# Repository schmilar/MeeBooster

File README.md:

# MeeBooster
Collection of 3 BoosterPacks for the Texas Instruments MSP432 Launchpad that aim to recreate the MeeBlip synthesizer on a different hardware platform.

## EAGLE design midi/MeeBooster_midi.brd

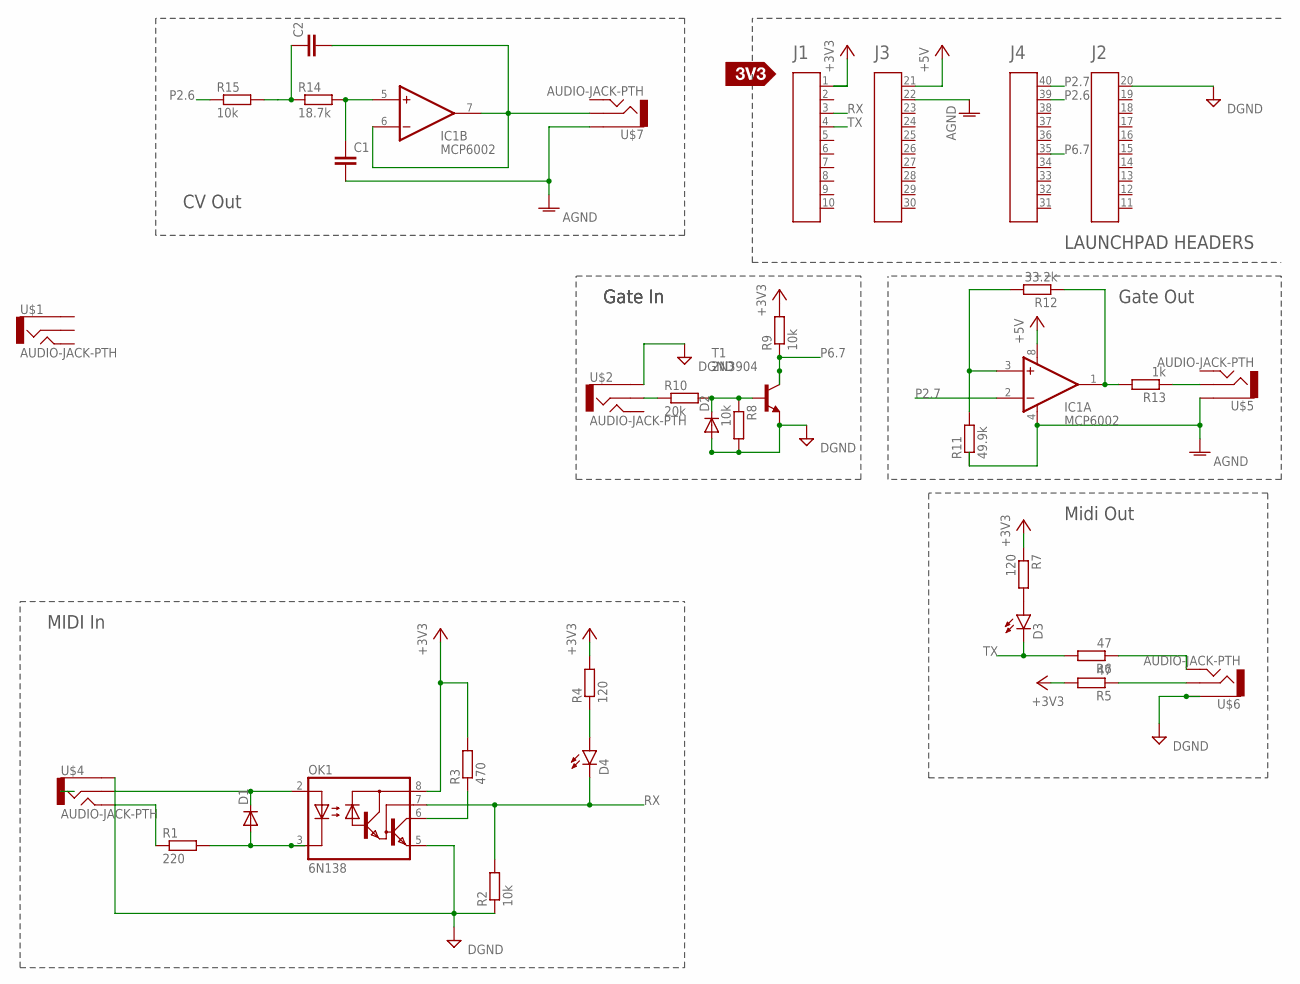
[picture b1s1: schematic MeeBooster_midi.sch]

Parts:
A1: HEADER4X10-BOOSTERPACK; 4X10-BOOSTERPACK
C1, C2: CAP0603-CAP; 0603-CAP
D1, D2: DIODE1N4148; DIODE-1N4148
D3, D4: LED5MM
IC1: MCP6002; DIL08
OK1: 6N138; DIL08
R1: 220; M1206
R2, R8, R9, R15: 10k; M1206
R3: 470; M1206
R4, R7: 120; M1206
R5, R6: 47; M1206
R10: 20k; M1206
R11: 49.9k; M1206
R12: 33.2k; M1206
R13: 1k; M1206
R14: 18.7k; M1206
T1: 2N3904; TO92
U$1, U$2, U$4, U$5, U$6, U$7: AUDIO-JACK-PTH; AUDIO-JACK
U$3: SILK_3V3_TAG

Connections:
5V: A1.1
+3V3: OK1.8 (VCC), R3.2, R4.2, R5.2, R7.1, R9.2
+5V: A1.21, IC1.8 (V+)
AGND: A1.22, C1.2, IC1.4 (V-), R11.1, U$5.1, U$7.1
DGND: A1.20, D2.A, OK1.5 (GND), R2.1, R8.2, T1.3 (E), U$2.1, U$4.1, U$6.1
unnamed: D1.C, OK1.2 (A), U$4.2
unnamed: D1.A, OK1.3 (C), R1.2
unnamed: D2.C, R8.1, R10.2, T1.2 (B)
unnamed: OK1.6 (VO), R3.1
unnamed: R1.1, U$4.5
unnamed: R5.1, U$6.2
unnamed: R6.1, U$6.5
unnamed: D3.A, R7.2
unnamed: D4.A, R4.1
unnamed: R10.1, U$2.2
unnamed: IC1.1 (OUT), R12.1, R13.2
unnamed: IC1.3 (+IN), R11.2, R12.2
unnamed: C2.2, IC1.6 (-IN), IC1.7 (OUT)
unnamed: R13.1, U$5.2
unnamed: C1.1, IC1.5 (+IN), R14.2
unnamed: C2.1, R14.1, R15.2
P2.6: A1.39, R15.1
P2.7: A1.40, IC1.2 (-IN)
P6.7: A1.35, R9.1, T1.1 (C)
RX: A1.3, D4.K (C), OK1.7 (VB), R2.2
TX: A1.4, D3.K (C), R6.2

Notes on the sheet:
LAUNCHPAD HEADERS
Midi Out
MIDI In
Gate In
Gate Out
CV Out

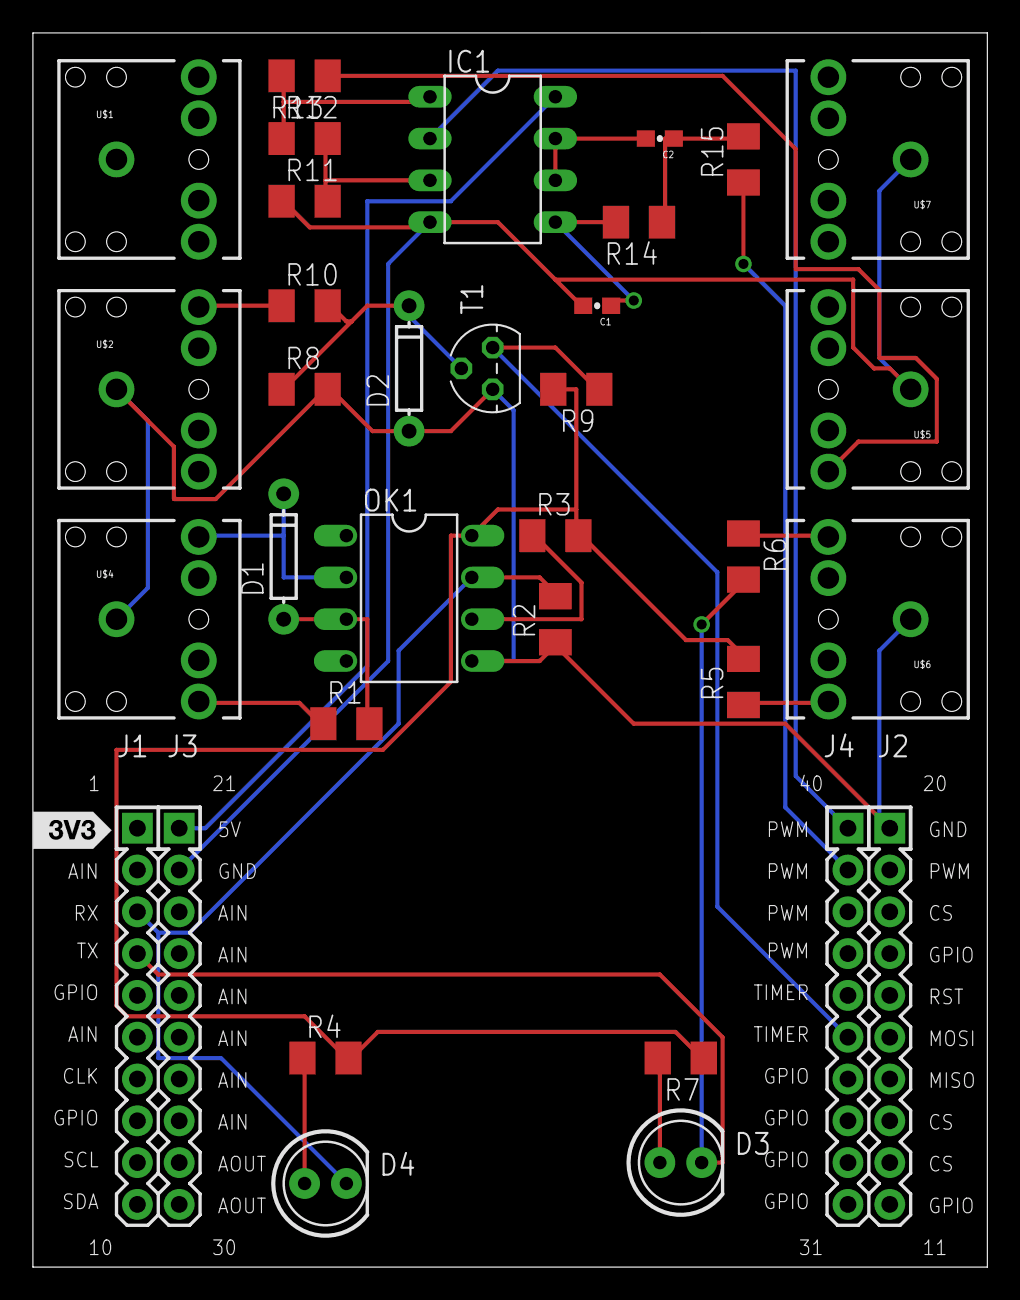
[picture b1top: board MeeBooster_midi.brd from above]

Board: 2 copper layers, 58.0 x 75.0 mm, 32 parts (0 on the bottom side), 25 nets.

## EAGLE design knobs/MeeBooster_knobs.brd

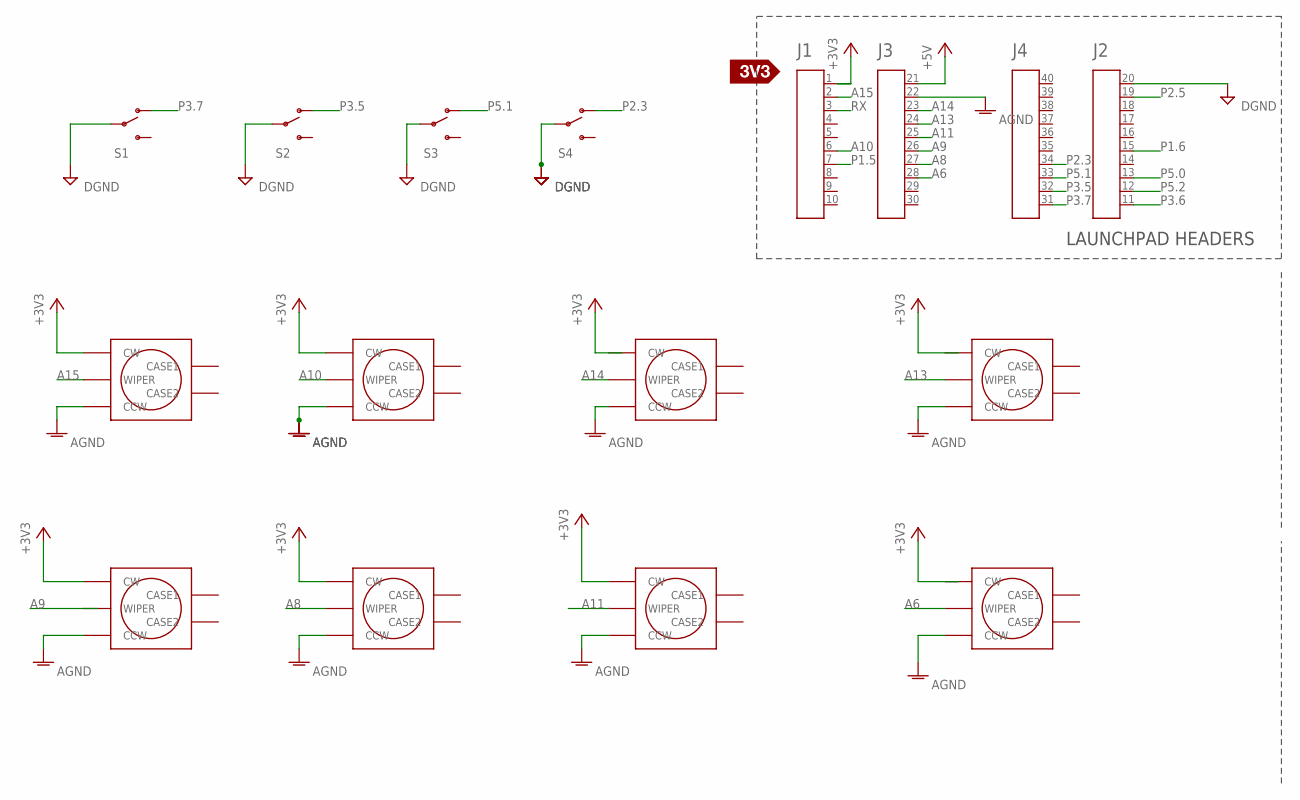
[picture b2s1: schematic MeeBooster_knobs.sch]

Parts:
A1: HEADER4X10-BOOSTERPACK; 4X10-BOOSTERPACK
S1, S2, S3, S4: SWITCH-SPSTPTH; SWITCH-SPDT
U$1, U$2, U$4, U$5, U$6, U$7, U$8, U$9: VACOLOCO_EVUFRK09_POT; VACOLOCO_EVUF
U$3: SILK_3V3_TAG

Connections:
5V: A1.1
+3V3: U$1.CW, U$2.CW, U$6.CW, U$7.CW, U$8.CW
+5V: A1.21
A6: A1.28, U$9.WIPER
A8: A1.27, U$7.WIPER
A9: A1.26
A10: A1.6, U$2.WIPER
A11: A1.25, U$8.WIPER
A13: A1.24, U$5.WIPER
A14: A1.23, U$4.WIPER
A15: A1.2, U$1.WIPER
AGND: A1.22, U$1.CCW, U$2.CCW, U$4.CCW, U$5.CCW, U$6.CCW, U$7.CCW, U$8.CCW, U$9.CCW
DGND: A1.20, S1.2, S2.2, S3.2, S4.2
P1.5: A1.7
P1.6: A1.15
P2.3: A1.34, S4.1 (O)
P2.5: A1.19
P3.5: A1.32, S2.1 (O)
P3.6: A1.11
P3.7: A1.31, S1.1 (O)
P5.0: A1.13
P5.1: A1.33, S3.1 (O)
P5.2: A1.12
RX: A1.3

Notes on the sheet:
LAUNCHPAD HEADERS

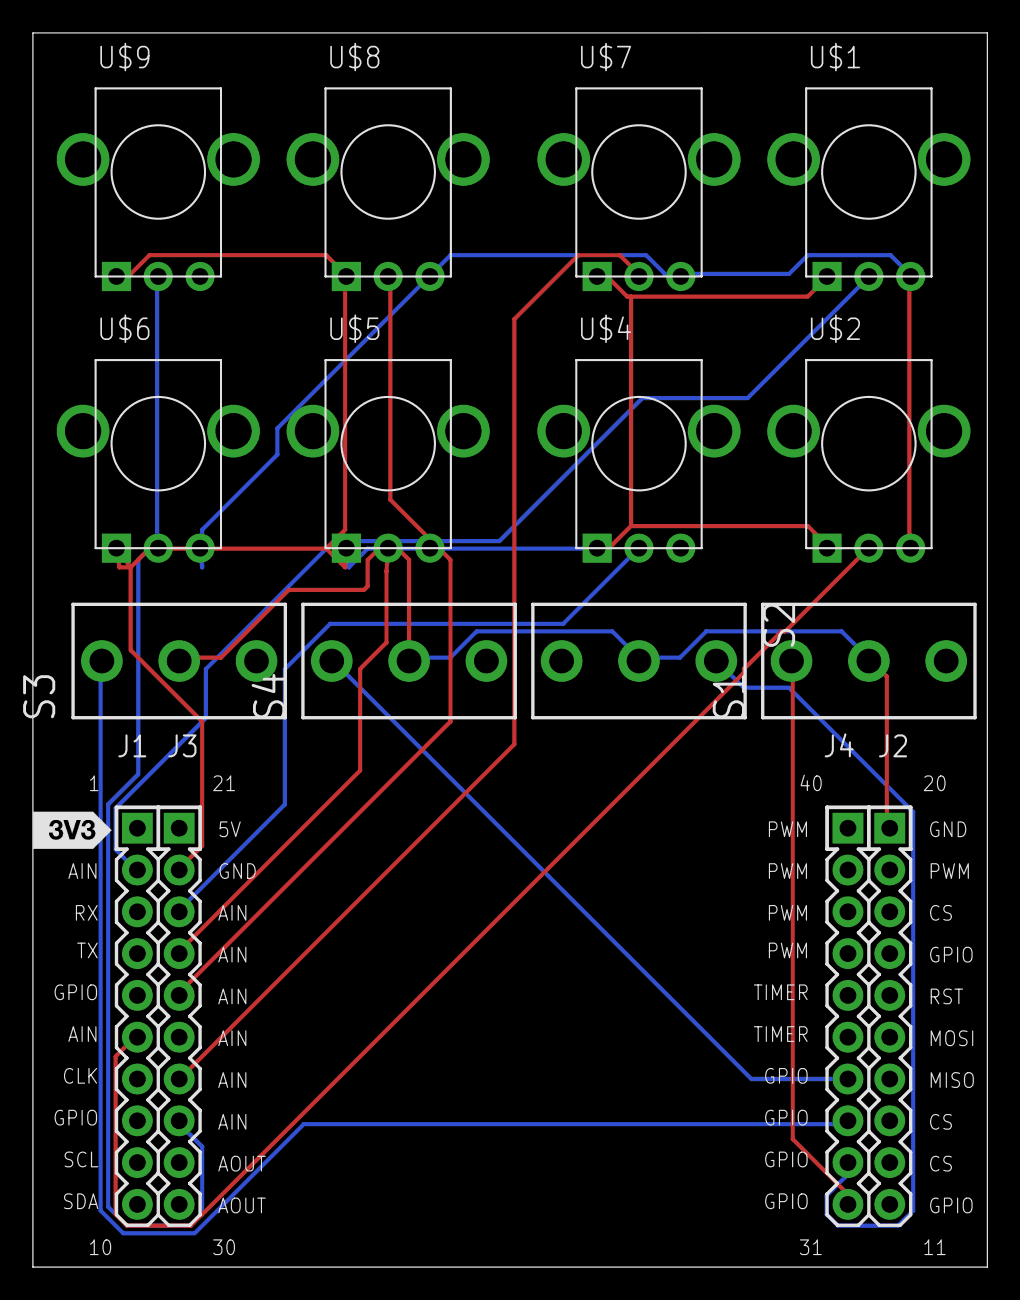
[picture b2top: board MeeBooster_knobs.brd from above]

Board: 2 copper layers, 58.0 x 75.0 mm, 14 parts (0 on the bottom side), 14 nets.

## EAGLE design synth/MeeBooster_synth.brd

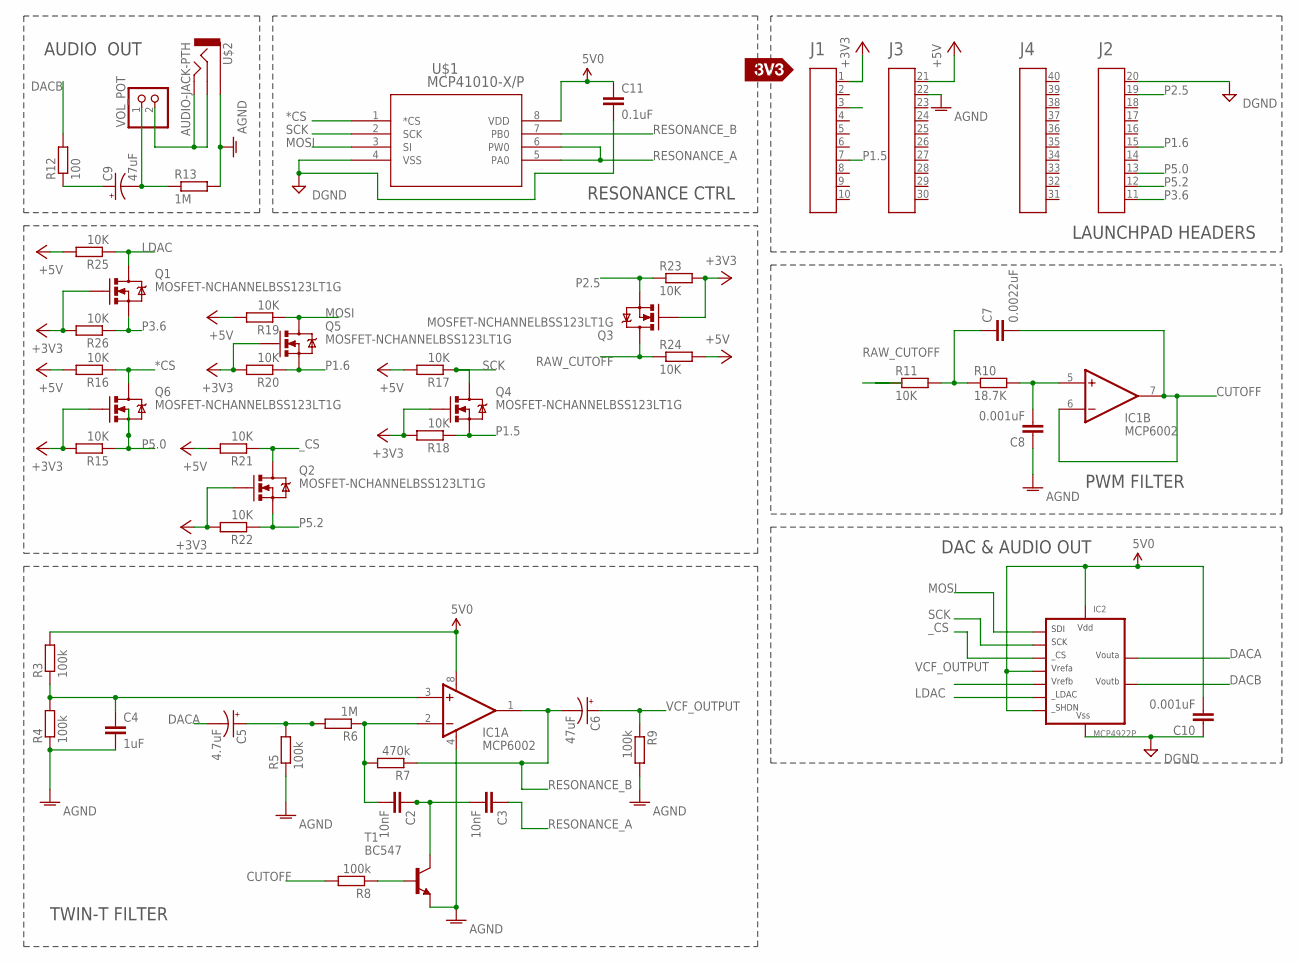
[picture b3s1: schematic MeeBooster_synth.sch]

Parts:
A1: HEADER4X10-BOOSTERPACK; 4X10-BOOSTERPACK
C2, C3: 10nF; 0603-CAP
C4: 1uF; 0603-CAP
C5: 4.7uF; PANASONIC_C
C6, C9: 47uF; PANASONIC_D
C7: 0.0022uF; 0603-CAP
C8, C10: 0.001uF; 0603-CAP
C11: 0.1uF; C0603
IC1: MCP6002; DIL08
IC2: MCP4922P; DIL14
Q1, Q2, Q3, Q4, Q5, Q6: MOSFET-NCHANNELBSS123LT1G; SOT23-3
R3, R4, R5, R8, R9: 100k; M1206
R6, R13: 1M; M1206
R7: 470k; M1206
R10: 18.7K; M1206
R11, R15, R16, R17, R18, R19, R20, R21, R22, R23, R24, R25, R26: 10K; M1206
R12: 100; M1206
T1: BC547; TO92
U$1: MCP41010-X/P; PDIP8_300MC
U$2: AUDIO-JACK-PTH; AUDIO-JACK
U$3: SILK_3V3_TAG
VOL_POT: PINHD-1X2; 1X02

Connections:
5V: A1.1, C10.2, C11.1, IC1.8 (V+), IC2.1 (VDD), IC2.9 (SHDN), IC2.13 (VREFA), R3.2, U$1.8 (VDD)
*CS: Q6.3 (D), R16.1, U$1.1 (*CS)
+3V3: Q1.1 (G), Q2.1 (G), Q3.1 (G), Q4.1 (G), Q5.1 (G), Q6.1 (G), R15.2, R18.2, R20.2, R22.2, R23.2, R26.2
+5V: A1.21, R16.2, R17.2, R19.2, R21.2, R24.2, R25.2
AGND: A1.22, C4.2, C8.1, IC1.4 (V-), R4.1, R5.1, R9.2, R13.2, T1.1 (E), U$2.1
CUTOFF: C7.2, IC1.6 (-IN), IC1.7 (OUT), R8.2
DACA: C5.-, IC2.14 (VOUTA)
DACB: IC2.10 (VOUTB), R12.2
DGND: A1.20, C10.1, C11.2, IC2.12 (VSS), U$1.4 (VSS)
FROM_VOL_POT: U$2.2, U$2.5, VOL_POT.2
LDAC: IC2.8 (LDAC), Q1.3 (D), R25.1
MOSI: IC2.5 (SDI), Q5.3 (D), R19.1, U$1.3 (SI)
unnamed: C4.1, IC1.3 (+IN), R3.1, R4.2
unnamed: C9.+, R12.1
unnamed: C2.2, IC1.2 (-IN), R6.1, R7.2
unnamed: C2.1, C3.2, T1.3 (C)
unnamed: C5.+, R5.2, R6.2
unnamed: R8.1, T1.2 (B)
unnamed: C8.2, IC1.5 (+IN), R10.2
unnamed: C7.1, R10.1, R11.2
P1.5: A1.7, Q4.2 (S), R18.1
P1.6: A1.15, Q5.2 (S), R20.1
P2.5: A1.19, Q3.2 (S), R23.1
P3.6: A1.11, Q1.2 (S), R26.1
P5.0: A1.13, Q6.2 (S), R15.1
P5.2: A1.12, Q2.2 (S), R22.1
RAW_CUTOFF: Q3.3 (D), R11.1, R24.1
RESONANCE_A: C3.1, U$1.5 (PA0), U$1.6 (PW0)
RESONANCE_B: C6.-, IC1.1 (OUT), R7.1, U$1.7 (PB0)
RX: A1.3
SCK: IC2.4 (SCK), Q4.3 (D), R17.1, U$1.2 (SCK)
TO_VOL_POT: C9.-, R13.1, VOL_POT.1
VCF_OUTPUT: C6.+, IC2.11 (VREFB), R9.1
_CS: IC2.3 (CS), Q2.3 (D), R21.1

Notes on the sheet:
LAUNCHPAD HEADERS
PWM FILTER
DAC & AUDIO OUT
TWIN-T FILTER
RESONANCE CTRL
AUDIO OUT

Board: 2 copper layers, 47 parts (0 on the bottom side), 33 nets, no tracks yet.

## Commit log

2016-03-04 Create LICENSE
2016-03-04 Schematics for synth booster
2016-03-04 Added Schematics and Board Layout for knobs BoosterPack
2016-03-04 Added schematics and first board layout for midi Boosterpack
2016-03-04 Pdf Export of schematics

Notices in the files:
parts and their libraries:
SparkFun-LED: Licensing: Creative Commons ShareAlike 4.0 International - https://creativecommons.org/licenses/by-sa/4.0
